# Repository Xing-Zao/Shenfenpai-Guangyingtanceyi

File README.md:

# 灵笼身份牌和光影探测仪软硬件开源资料

[灵笼身份牌](https://www.bilibili.com/video/BV1do4y1f7v5) 和 灵笼光[影探测仪](https://www.bilibili.com/video/BV1FK411F7UJ)的配套软硬件资料。

## 如何找到文件
- Light_detector 光影探测仪全部资料
- Badge 身份牌全部资料

每个文件夹下面都包含以下文件：
### 00_Priority README
该目录下存放了该控制板项目的全部**技术文档**，对该项目的程序源码、PCB设计都有详细说明，请首先阅读。
>文档目前尚未编写完成
>
### 01_Firmware
该目录下存放了 **软件/程序** 相关的全部源文件

### 02_Electronics
该目录下存放了 **电路/PCB** 相关的全部源文件

### 04_others
即不属于 软件/程序 也不属于 电路/PCB，但和本项目相关的其它文件

###  README.txt
每个文件夹下都有该文档，请**首先阅读**。这包含有其所处文件夹的阅读索引及一些重要说明。

## 支持

资料还在修改中，为了获得最佳的配置和故障排除帮助，请使用以下资源：
- 哔哩哔哩：[猩造](https://space.bilibili.com/16614468/)  
- 微信加群：

## 许可协议

FeixueMask 是遵循 [GPL license](/LICENSE) 协议发行的，因为我们相信开放式开发。 GPL附带了权利和义务。 无论您使用 FeixueMask 固件作为开源产品还是封闭源产品的驱动程序，都必须保持 FeixueMask 开放，并且必须根据要求向最终用户提供兼容的 FeixueMask 源代码。 遵守 FeixueMask 许可证的最直接方法是在 Github 上制作 FeixueMask 的分支，执行您的修改，并将用户引导到您修改后的分支。

虽然我们不能禁止在具有封闭源代码或有专利保护的产品中使用此代码，但我们还是希望您选择其他固件，或者最好自己制作。

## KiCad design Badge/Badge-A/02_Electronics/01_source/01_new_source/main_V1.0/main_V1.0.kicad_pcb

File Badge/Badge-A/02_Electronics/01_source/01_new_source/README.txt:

A1.0  2020-08-18
  原理图错误：
    1. Q1 引脚1、2颠倒（main、LED）
    2. RX接MCU引脚错误，应接PA10（main）
    3. 电容C2~5 值错误，应为 0.1uF（main）

V1.0  2020-08-21
   版本更新：
     1. 修复上一版设计错误（main、LED）
     2. LED灯板重新设计，三色灯改为单色灯（LED）
  版本错误：

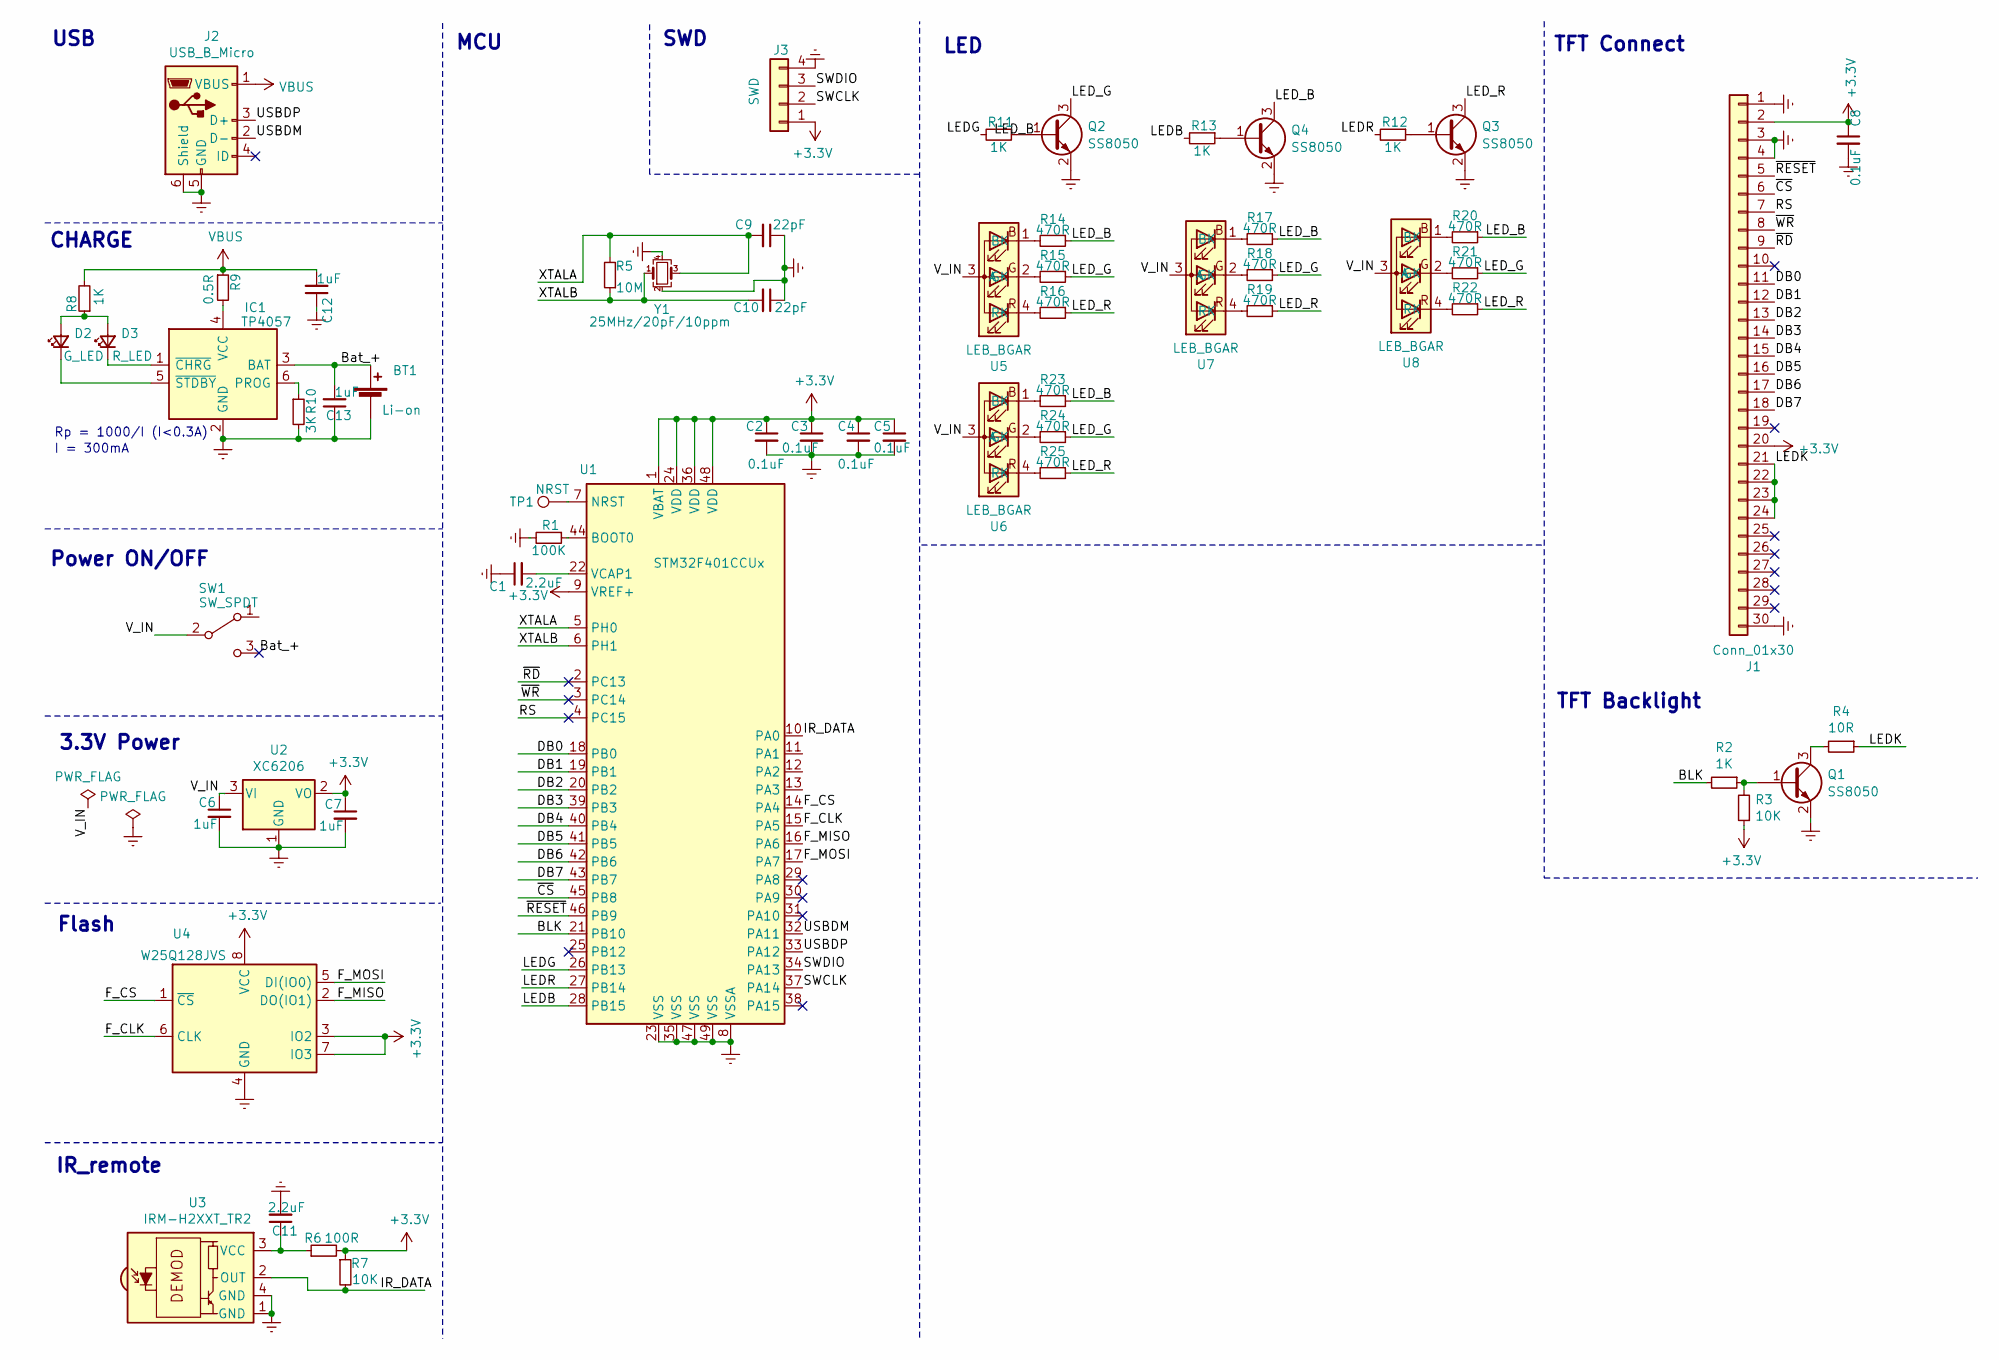
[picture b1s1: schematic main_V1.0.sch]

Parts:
BT1: Li-on; Pad-2.2mm_1.5x1.5
C1, C11: 2.2uF; C_0603_1608Metric
C2, C3, C4, C5, C8: 0.1uF; C_0402_1005Metric
C6, C7, C12, C13: 1uF; C_0603_1608Metric
C9, C10: 22pF; C_0603_1608Metric
D2: G_LED; LED_0603_1608Metric
D3: R_LED; LED_0603_1608Metric
IC1: TP4057; SOT-23-6; Manufacturer_Part_Number TP4057-42-SOT26-R
J1: Conn_01x30; FFC-1x30-1MP_P0.5mm_Horizontal
J2: USB_B_Micro; USB_Micro-B_Molex_Sink
J3: SWD; Con-1x4-P1.25mm
Q1, Q2, Q3, Q4: SS8050; SOT-23
R1: 100K; R_0603_1608Metric
R2, R8, R11, R12, R13: 1K; R_0402_1005Metric
R3, R7: 10K; R_0603_1608Metric
R4: 10R; R_0603_1608Metric
R5: 10M; R_0603_1608Metric
R6: 100R; R_0603_1608Metric
R9: 0.5R; R_0805_2012Metric
R10: 3K; R_0603_1608Metric
R14, R15, R16, R17, R18, R19, R20, R21, R22, R23, R24, R25: 470R; R_0402_1005Metric
SW1: SW_SPDT; MSKT-12C00-switch-smd
TP1: NRST; TestPoint_Pad_D1.0mm
U1: STM32F401CCUx; QFN-48-1EP_7x7mm_P0.5mm_EP5.6x5.6mm
U2: XC6206; SOT-23
U3: IRM-H2XXT_TR2
U4: W25Q128JVS; SON127P800X600X80-9N-D
U5, U6, U7, U8: LEB_BGAR; RGB-3510-Side-Common_anode
Y1: 25MHz/20pF/10ppm; Crystal_SMD_2520-4Pin_2.5x2.0mm

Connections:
+3V3: C2.1, C3.1, C4.1, C5.1, C7.1, C8.1, J1.2, J1.20, J3.1, R3.1, R6.2, R7.1, U1.1 (VBAT), U1.9 (VREF+), U1.24 (VDD), U1.36 (VDD), U1.48 (VDD), U2.2 (VO), U4.3 (IO2), U4.7 (IO3), U4.8 (VCC)
/BLK: R2.2, U1.21 (PB10)
/Bat_+: BT1.1 (+), C13.2, IC1.3 (BAT), SW1.3 (C)
/DB0: J1.11, U1.18 (PB0)
/DB1: J1.12, U1.19 (PB1)
/DB2: J1.13, U1.20 (PB2)
/DB3: J1.14, U1.39 (PB3)
/DB4: J1.15, U1.40 (PB4)
/DB5: J1.16, U1.41 (PB5)
/DB6: J1.17, U1.42 (PB6)
/DB7: J1.18, U1.43 (PB7)
/F_CLK: U1.15 (PA5), U4.6 (CLK)
/F_CS: U1.14 (PA4), U4.1 (~CS)
/F_MISO: U1.16 (PA6), U4.2 (DO(IO1))
/F_MOSI: U1.17 (PA7), U4.5 (DI(IO0))
/IR_DATA: R7.2, U1.10 (PA0), U3.2 (OUT)
/LEDB: R13.2, U1.28 (PB15)
/LEDG: R11.2, U1.26 (PB13)
/LEDK: J1.21, J1.22, J1.23, J1.24, R4.1
/LEDR: R12.2, U1.27 (PB14)
/LED_B: Q4.3 (C), R14.1, R17.1, R20.1, R23.1
/LED_G: Q2.3 (C), R15.1, R18.1, R21.1, R24.1
/LED_R: Q3.3 (C), R16.1, R19.1, R22.1, R25.1
/RS: J1.7, U1.4 (PC15)
/SWCLK: J3.2, U1.37 (PA14)
/SWDIO: J3.3, U1.34 (PA13)
/USBDM: J2.2 (D-), U1.32 (PA11)
/USBDP: J2.3 (D+), U1.33 (PA12)
/V_IN: C6.1, SW1.2 (B), U2.3 (VI), U5.3 (A), U6.3 (A), U7.3 (A), U8.3 (A)
/XTALA: C9.2, R5.2, U1.5 (PH0), Y1.3
/XTALB: C10.2, R5.1, U1.6 (PH1), Y1.1
/~CS: J1.6, U1.45 (PB8)
/~RD: J1.9, U1.2 (PC13)
/~RESET: J1.5, U1.46 (PB9)
/~WR: J1.8, U1.3 (PC14)
Earth: BT1.2 (-), C1.1, C2.2, C3.2, C4.2, C5.2, C6.2, C7.2, C8.2, C9.1, C10.1, C11.2, C12.1, C13.1, IC1.2 (GND), J1.1, J1.3, J1.4, J1.30, J2.5 (GND), J2.6 (Shield), J3.4, Q1.2 (E), Q2.2 (E), Q3.2 (E), Q4.2 (E), R1.2, R10.2, U1.8 (VSSA), U1.23 (VSS), U1.35 (VSS), U1.47 (VSS), U1.49 (VSS), U2.1 (GND), U3.1 (GND), U3.4 (GND), U4.4 (GND), Y1.2, Y1.4
unnamed: C1.2, U1.22 (VCAP1)
unnamed: C11.1, R6.1, U3.3 (VCC)
unnamed: D2.1 (K), IC1.5 (~STDBY)
unnamed: D2.2 (A), D3.2 (A), R8.1
unnamed: D3.1 (K), IC1.1 (~CHRG)
unnamed: IC1.4 (VCC), R9.2
unnamed: IC1.6 (PROG), R10.1
unnamed: Q1.1 (B), R2.1, R3.2
unnamed: Q1.3 (C), R4.2
unnamed: Q2.1 (B), R11.1
unnamed: Q3.1 (B), R12.1
unnamed: Q4.1 (B), R13.1
unnamed: R1.1, U1.44 (BOOT0)
unnamed: R14.2, U5.1 (BK)
unnamed: R15.2, U5.2 (GK)
unnamed: R16.2, U5.4 (RK)
unnamed: R17.2, U7.1 (BK)
unnamed: R18.2, U7.2 (GK)
unnamed: R19.2, U7.4 (RK)
unnamed: R20.2, U8.1 (BK)
unnamed: R21.2, U8.2 (GK)
unnamed: R22.2, U8.4 (RK)
unnamed: R23.2, U6.1 (BK)
unnamed: R24.2, U6.2 (GK)
unnamed: R25.2, U6.4 (RK)
unnamed: TP1.1, U1.7 (NRST)
VBUS: C12.2, J2.1 (VBUS), R8.2, R9.1

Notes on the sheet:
3.3V Power
Power ON/OFF
TFT Backlight
LED
TFT Connect
MCU
SWD
Rp = 1000/I (I<0.3A)
I = 300mA
USB
CHARGE
Flash
IR_remote

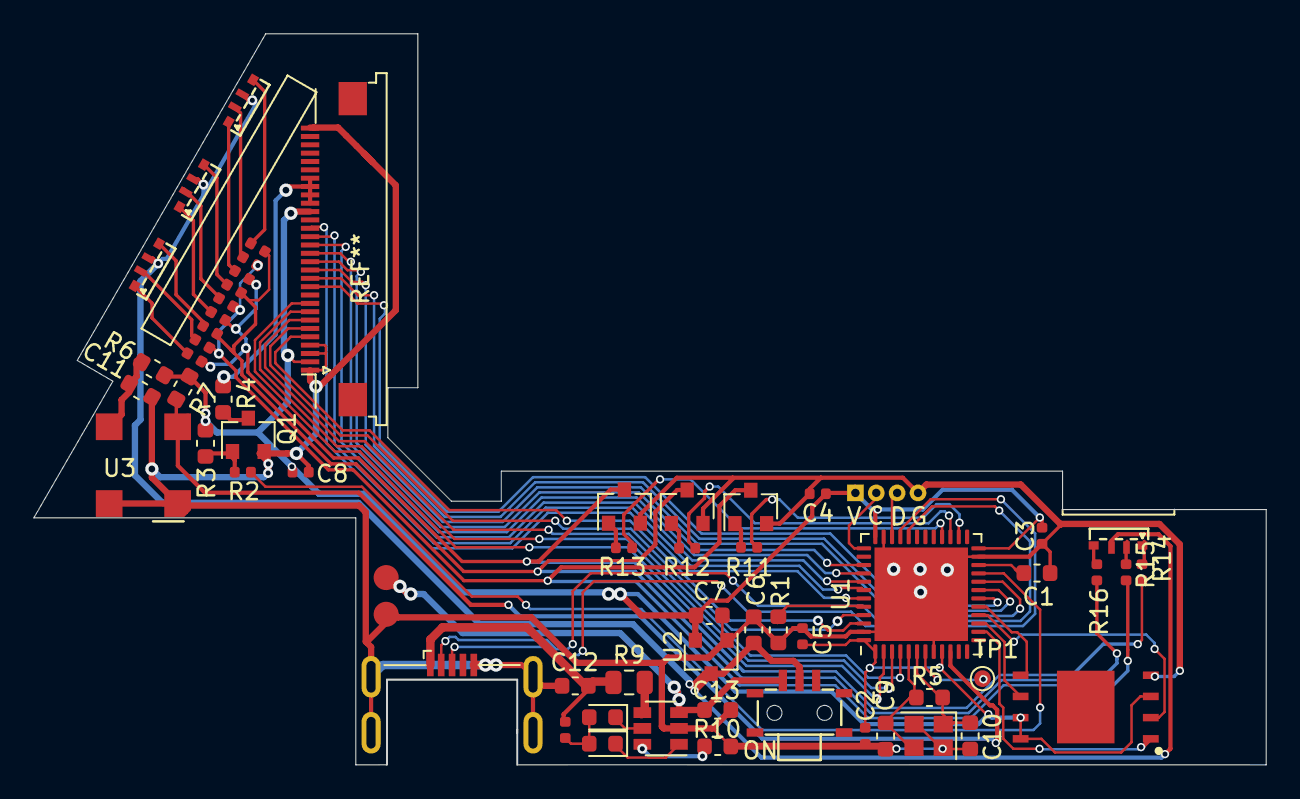
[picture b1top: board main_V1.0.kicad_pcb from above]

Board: 2 copper layers, 73.8 x 43.8 mm, 60 parts (0 on the bottom side), 63 nets.

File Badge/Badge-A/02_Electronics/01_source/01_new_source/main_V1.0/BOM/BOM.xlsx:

Reference | Quantity | Value | Footprint | Datasheet | Description | 采购建议
BT1 | 1 | Li-on | Pad-2.2mm_1.5x1.5 | ~ | 电池接口焊点，人工焊接 | 无需购买
C1 C11 | 2 | 2.2uF ±10% 6.3V/10V/16V | C_0603_1608Metric | ~ |  | 非指定厂家，符合：Value、Footprint 即可
C10 C9 | 2 | 22pF ±10% 6.3V/10V/16V | C_0603_1608Metric | ~ |  | 非指定厂家，符合：Value、Footprint 即可
C2 C3 C4 C5 C8 | 5 | 0.1uF ±10% 6.3V/10V/16V | C_0402_1005Metric | ~ |  | 非指定厂家，符合：Value、Footprint 即可
C6 C7 C12 C13 | 4 | 1uF ±10% 6.3V/10V/16V | C_0603_1608Metric | ~ |  | 非指定厂家，符合：Value、Footprint 即可
D2 | 1 | G_LED IF<25mA | LED_0603_1608Metric | ~ |  | 非指定厂家，符合：Value、Footprint 即可
D3 | 1 | R_LED IF<25mA | LED_0603_1608Metric | ~ |  | 非指定厂家，符合：Value、Footprint 即可
IC1 | 1 | TP4057 | SOT-23-6 | 见数据表：02-TP4057_2020-08-19.pdf | 锂电池充电芯片 | 指定厂家
J1 | 1 | Conn_01x30 | FFC-1x30-1MP_P0.5mm_Horizontal | 见数据表：03_FFCFPC连接器0.5MM间距30P卧贴抽拉式上接H1.2MM_2020-10-20.pdf | FFC 连接器 0.5mm间距 30P 卧贴抽拉式上接 H1.2mm | 指定厂家
J2 | 1 | USB_B_Micro | USB_Micro-B_Molex_Sink | 见数据表：04-MICRO_5SB型沉板式0.8四脚全插无导位有孔三边双卡端_2021-03-08.pdf | MICRO/5S B型沉板式0.8四脚全插无导位有孔三边双卡端 | 指定厂家
J3 | 1 | SWD | Con-1x4-P1.25mm | ~ | 下载调试接口，不焊接 | 无需购买
Q1 Q2 Q4 Q3 | 4 | SS8050 | SOT-23 | 见数据表：05-SS8050Y1200-350.pdf |  | 指定厂家
R1 | 1 | 100K ±5% 0.1W_1/16W | R_0603_1608Metric | ~ |  | 非指定厂家，符合：Value、Footprint 即可
R10 | 1 | 3K ±5% 0.1W_1/16W | R_0603_1608Metric | ~ |  | 非指定厂家，符合：Value、Footprint 即可
R14 R15 R16 R17 R18 R19 R20 R21 R22 R23 R24 R25 | 12 | 470R ±5% 0.1W_1/16W | R_0402_1005Metric | ~ |  | 非指定厂家，符合：Value、Footprint 即可
R2 R8 R11 R13 R12 | 5 | 1K ±5% 0.1W_1/16W | R_0402_1005Metric | ~ |  | 非指定厂家，符合：Value、Footprint 即可
R3 R7 | 2 | 10K ±5% 0.1W_1/16W | R_0603_1608Metric | ~ |  | 非指定厂家，符合：Value、Footprint 即可
R4 | 1 | 10R ±5% 0.1W_1/16W | R_0603_1608Metric | ~ |  | 非指定厂家，符合：Value、Footprint 即可
R5 | 1 | 10M ±5% 0.1W_1/16W | R_0603_1608Metric | ~ |  | 非指定厂家，符合：Value、Footprint 即可
R6 | 1 | 100R ±5% 0.1W_1/16W | R_0603_1608Metric | ~ |  | 非指定厂家，符合：Value、Footprint 即可
R9 | 1 | 0.5R ±5% 0.1W_1/16W | R_0805_2012Metric | ~ |  | 非指定厂家，符合：Value、Footprint 即可
SW1 | 1 | SW_SPDT | MSKT-12C00-switch-smd | 见数据表：10-开关规格.png | 侧贴拨动开关 | 指定厂家，淘宝：温州一键电子科技，型号MSKT-12C00 黑色
TP1 | 1 | NRST | TestPoint_Pad_D1.0mm | ~ | 测试焊点，不焊接 | 无需购买
U1 | 1 | STM32F401CCUx | QFN-48-1EP_7x7mm_P0.5mm_EP5.6x5.6mm | 见数据表：06-STM32F401CCU6_2016-08-16.pdf | 主控芯片，型号 STM32F401CCU6 | 指定厂家
U2 | 1 | XC6206 | SOT-23 | 见数据表：07-XC6206P302MR.pdf | 稳压降压芯片 | 指定厂家
U3 | 1 | IRM-H2XXT_TR2 | IRM-H2XXT_TR2 | 见数据表：08-红外线接收头38KHZ贴片_2017-09-18.PDF | 红外接收头 | 指定厂家
U4 | 1 | W25Q128JVS | SON127P800X600X80-9N-D | 见数据表：09-W25Q64JVZEIQ_2020-06-23.PDF | flash芯片，型号W25Q64JVIQ，封装WSON 8x6mm | 指定厂家
U5 U7 U8 U6 | 4 | LEB_BGAR | RGB-3510-Side-Common_anode | 见数据表：11-3510侧发RGB全彩_2020-09-04.PDF | 侧贴RGB全彩 | 指定厂家
Y1 | 1 | 25MHz/20pF/10ppm | Crystal_SMD_2520-4Pin_2.5x2.0mm | 见数据表：12-25M20PPM20PF-30+85℃_2018-07-26.PDF |  | 指定厂家
其它原件
 | 1 | 锂电池 | 尺寸：20x10x3mm 容量40mAh，带保护板 |  |  | 指定厂家，淘宝：裕辉达玩具数码电池户，型号301020 50mAh，带保护板
 | 1 | 1.9寸显示屏 | 1.9寸长条形IPS全视角170*320分辨率MCU接口 | 见数据表：13-TL019FQV01-B1263A_specification.pdf |  | 指定厂家，淘宝：深圳市显创液晶显示有限公司 型号：1.9寸长条形显示屏IPS全视角170*320分辨率
 | 1 | 背光板 | 18*8*1.3 |  | RGB侧面显示匀光板，需手工裁切 | 指定厂家，淘宝：深圳市宝晖光电 型号：18*8*1.3 白色背光板

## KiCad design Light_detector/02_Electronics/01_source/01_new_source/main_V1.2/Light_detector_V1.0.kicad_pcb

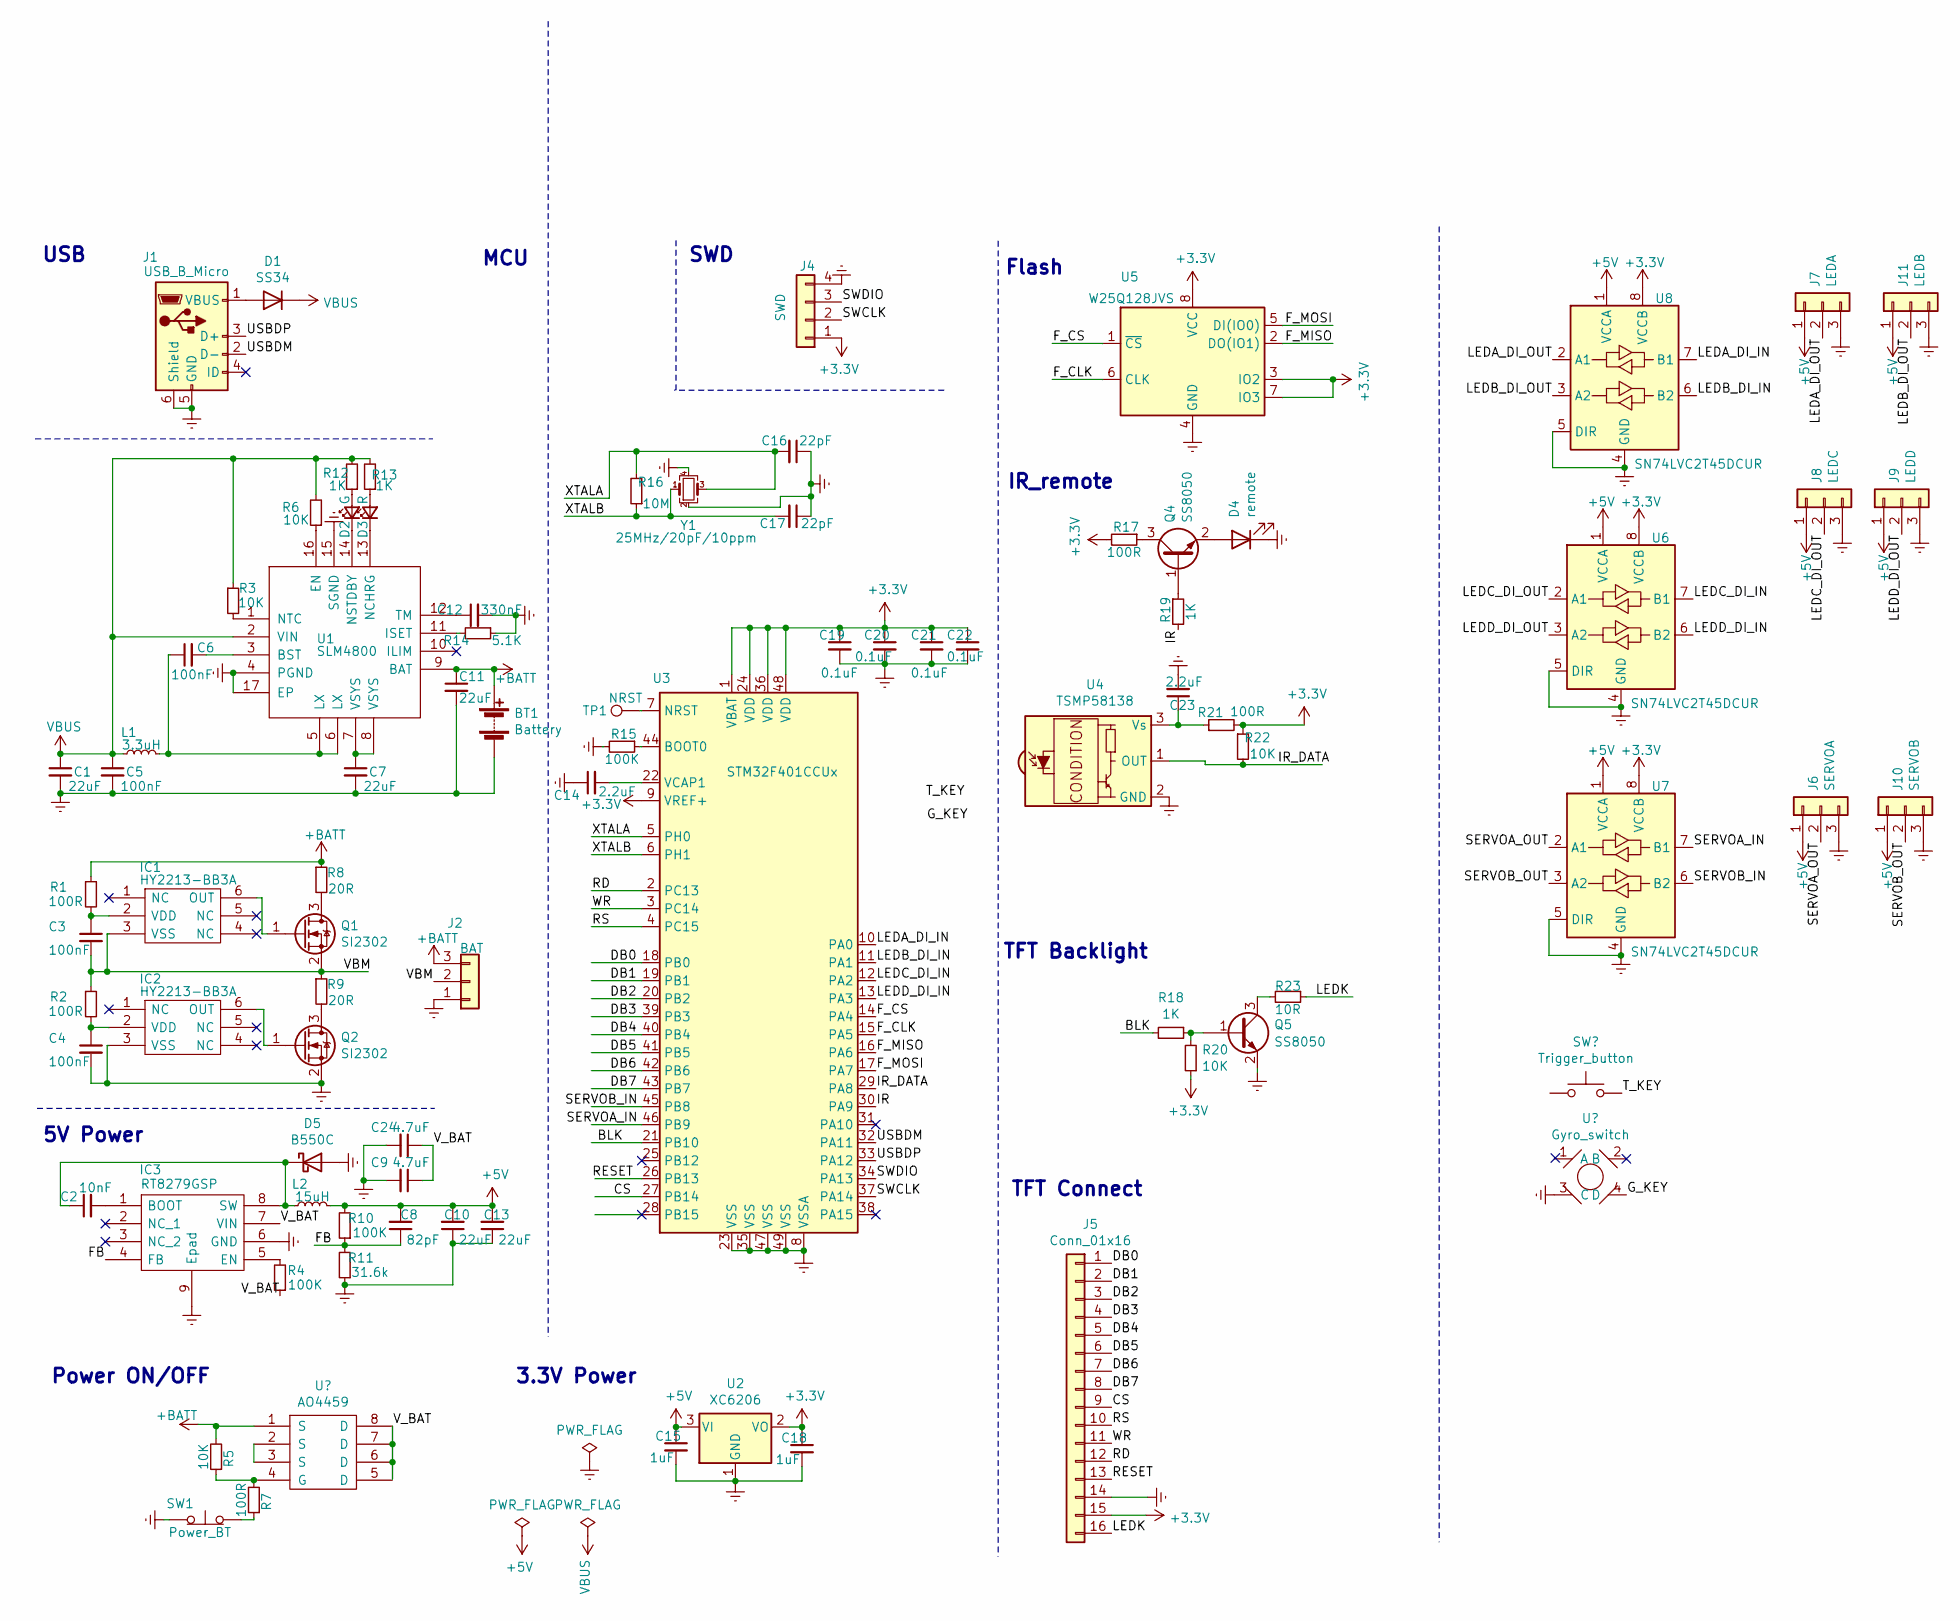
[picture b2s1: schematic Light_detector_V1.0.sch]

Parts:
BT1: Battery; JWT_A3963_1x02_P3.96mm_Vertical
C1, C7, C10, C11, C13: 22uF; C_1206_3216Metric
C2: 10nF; C_0402_1005Metric
C3, C4, C5, C6: 100nF; C_0402_1005Metric
C8: 82pF; C_0402_1005Metric
C9, C24: 4.7uF; C_1206_3216Metric
C12: 330nF; C_0402_1005Metric
C14, C23: 2.2uF; C_0603_1608Metric
C15, C18: 1uF; C_0603_1608Metric
C16, C17: 22pF; C_0402_1005Metric
C19, C20, C21, C22: 0.1uF; C_0402_1005Metric
D1: SS34; D_SMA
D2: G; LED_0603_1608Metric
D3: R; LED_0603_1608Metric
D4: remote; Con-2.5mm_0.9x1.7
D5: B550C; D_SMC
IC1, IC2: HY2213-BB3A; SOT95P280X140-6N; Manufacturer_Part_Number HY2213-BB3A
IC3: RT8279GSP; Diodes_SO-8EP; Manufacturer_Part_Number RT8279GSP
J1: USB_B_Micro; USB_Micro-B_Molex-105017-0001
J2: BAT; JST_XH_S3B-XH-A-1_1x03_P2.50mm_Horizontal
J4: SWD; PinHeader_1x04_P1.27mm_Vertical
J5: Conn_01x16; TE_1-1734839-6_1x16-1MP_P0.5mm_Horizontal
J6: SERVOA; PinHeader_1x03_P2.54mm_Horizontal
J7: LEDA; JST_XH_S3B-XH-A-1_1x03_P2.50mm_Horizontal
J8: LEDC; JST_XH_S3B-XH-A-1_1x03_P2.50mm_Horizontal
J9: LEDD; JST_XH_S3B-XH-A-1_1x03_P2.50mm_Horizontal
J10: SERVOB; PinHeader_1x03_P2.54mm_Horizontal
J11: LEDB; JST_XH_S3B-XH-A-1_1x03_P2.50mm_Horizontal
L1: 3.3uH; L_Sumida_CDMC6D28_7.25x6.5mm
L2: 15uH; L_Neosid_SM-PIC1004H
Q1, Q2: SI2302; SOT-23
Q4, Q5: SS8050; SOT-23
R1, R2, R7: 100R; R_0402_1005Metric
R3, R5, R6, R20, R22: 10K; R_0402_1005Metric
R4, R10, R15: 100K; R_0402_1005Metric
R8, R9: 20R; R_2512_6332Metric
R11: 31.6k; R_0402_1005Metric
R12, R13, R18, R19: 1K; R_0402_1005Metric
R14: 5.1K; R_0402_1005Metric
R16: 10M; R_0402_1005Metric
R17, R21: 100R; R_0603_1608Metric
R23: 10R; R_0603_1608Metric
SW1: Power_BT; JST_XH_S2B-XH-A-1_1x02_P2.50mm_Horizontal
TP1: NRST; TestPoint_Pad_D1.0mm
U1: SLM4800; QFN-16-1EP_4x4mm_P0.65mm_EP2.1x2.1mm_ThermalVias
U2: XC6206; SOT-23
U3: STM32F401CCUx; QFN-48-1EP_7x7mm_P0.5mm_EP5.6x5.6mm
U4: TSMP58138; Vishay_MINICAST-3Pin
U5: W25Q128JVS; SON127P800X600X80-9N-D
U6, U7, U8: SN74LVC2T45DCUR; VSSOP-8_2.4x2.1mm_P0.5mm
Y1: 25MHz/20pF/10ppm; Crystal_SMD_2520-4Pin_2.5x2.0mm

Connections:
+3V3: C18.1, C19.1, C20.1, C21.1, C22.1, J4.1, J5.15, R17.2, R20.1, R21.2, R22.1, U2.2 (VO), U3.1 (VBAT), U3.9 (VREF+), U3.24 (VDD), U3.36 (VDD), U3.48 (VDD), U5.3 (IO2), U5.7 (IO3), U5.8 (VCC), U6.8 (VCCB), U7.8 (VCCB), U8.8 (VCCB)
+5V: C8.2, C10.2, C13.2, C15.1, J6.1, J7.1, J8.1, J9.1, J10.1, J11.1, L2.2, R10.2, U2.3 (VI), U6.1 (VCCA), U7.1 (VCCA), U8.1 (VCCA)
+BATT: BT1.1 (+), C11.1, J2.3, R1.1, R5.2, R8.1, U1.9 (BAT); also elsewhere on the board
/BLK: R18.2, U3.21 (PB10)
/CS: J5.9, U3.27 (PB14)
/DB0: J5.1, U3.18 (PB0)
/DB1: J5.2, U3.19 (PB1)
/DB2: J5.3, U3.20 (PB2)
/DB3: J5.4, U3.39 (PB3)
/DB4: J5.5, U3.40 (PB4)
/DB5: J5.6, U3.41 (PB5)
/DB6: J5.7, U3.42 (PB6)
/DB7: J5.8, U3.43 (PB7)
/FB: C8.1, IC3.4 (FB), R10.1, R11.2
/F_CLK: U3.15 (PA5), U5.6 (CLK)
/F_CS: U3.14 (PA4), U5.1 (~CS)
/F_MISO: U3.16 (PA6), U5.2 (DO(IO1))
/F_MOSI: U3.17 (PA7), U5.5 (DI(IO0))
/IR: R19.2, U3.30 (PA9)
/IR_DATA: R22.2, U3.29 (PA8), U4.1 (OUT)
/LEDA_DI_IN: U3.10 (PA0), U8.7 (B1)
/LEDA_DI_OUT: J7.2, U8.2 (A1)
/LEDB_DI_IN: U3.11 (PA1), U8.6 (B2)
/LEDB_DI_OUT: J11.2, U8.3 (A2)
/LEDC_DI_IN: U3.12 (PA2), U6.7 (B1)
/LEDC_DI_OUT: J8.2, U6.2 (A1)
/LEDD_DI_IN: U3.13 (PA3), U6.6 (B2)
/LEDD_DI_OUT: J9.2, U6.3 (A2)
/LEDK: J5.16, R23.1
/RD: J5.12, U3.2 (PC13)
/RESET: J5.13, U3.26 (PB13)
/RS: J5.10, U3.4 (PC15)
/SERVOA_IN: U3.46 (PB9), U7.7 (B1)
/SERVOA_OUT: J6.2, U7.2 (A1)
/SERVOB_IN: U3.45 (PB8), U7.6 (B2)
/SERVOB_OUT: J10.2, U7.3 (A2)
/SWCLK: J4.2, U3.37 (PA14)
/SWDIO: J4.3, U3.34 (PA13)
/USBDM: J1.2 (D-), U3.32 (PA11)
/USBDP: J1.3 (D+), U3.33 (PA12)
/VBM: C3.2, IC1.3 (VSS), J2.2, Q1.2 (S), R2.1, R9.1
/V_BAT: C9.1, C24.1, IC3.7 (VIN), R4.1; also elsewhere on the board
/WR: J5.11, U3.3 (PC14)
/XTALA: C16.2, R16.2, U3.5 (PH0), Y1.3
/XTALB: C17.2, R16.1, U3.6 (PH1), Y1.1
Earth: BT1.2 (-), C1.2, C4.2, C5.2, C7.2, C9.2, C10.1, C11.2, C12.2, C13.1, C14.1, C15.2, C16.1, C17.1, C18.2, C19.2, C20.2, C21.2, C22.2, C23.2, C24.2, D4.1 (K), D5.2 (A), IC2.3 (VSS), IC3.6 (GND), IC3.9 (Epad), J1.5 (GND), J1.6 (Shield), J2.1, J4.4, J5.14, J6.3, J7.3, J8.3, J9.3, J10.3, J11.3, Q2.2 (S), Q5.2 (E), R11.1, R14.1, R15.2, SW1.1 (A), U1.4 (PGND), U1.15 (SGND), U1.17 (EP), U2.1 (GND), U3.8 (VSSA), U3.23 (VSS), U3.35 (VSS), U3.47 (VSS), U3.49 (VSS), U4.2 (GND), U5.4 (GND), U6.4 (GND), U6.5 (DIR), U7.4 (GND), U7.5 (DIR), U8.4 (GND), U8.5 (DIR), Y1.2, Y1.4
unnamed: C2.1, D5.1 (K), IC3.8 (SW), L2.1
unnamed: C2.2, IC3.1 (BOOT)
unnamed: C3.1, IC1.2 (VDD), R1.2
unnamed: C4.1, IC2.2 (VDD), R2.2
unnamed: C6.1, L1.2, U1.5 (LX), U1.6 (LX)
unnamed: C6.2, U1.3 (BST)
unnamed: C7.1, U1.7 (VSYS), U1.8 (VSYS)
unnamed: C12.1, U1.12 (TM)
unnamed: C14.2, U3.22 (VCAP1)
unnamed: C23.1, R21.1, U4.3 (Vs)
unnamed: D1.2 (A), J1.1 (VBUS)
unnamed: D2.1 (K), U1.14 (NSTDBY)
unnamed: D2.2 (A), R12.1
unnamed: D3.1 (K), U1.13 (NCHRG)
unnamed: D3.2 (A), R13.1
unnamed: D4.2 (A), Q4.2 (E)
unnamed: IC1.6 (OUT), Q1.1 (G)
unnamed: IC2.6 (OUT), Q2.1 (G)
unnamed: IC3.5 (EN), R4.2
unnamed: Q1.3 (D), R8.2
unnamed: Q2.3 (D), R9.2
unnamed: Q4.1 (B), R19.1
unnamed: Q4.3 (C), R17.1
unnamed: Q5.1 (B), R18.1, R20.2
unnamed: Q5.3 (C), R23.2
unnamed: R3.2, U1.1 (NTC)
unnamed 81: R5.1, R7.2; also elsewhere on the board
unnamed: R6.1, U1.16 (EN)
unnamed: R7.1, SW1.2 (B)
unnamed: R14.2, U1.11 (ISET)
unnamed: R15.1, U3.44 (BOOT0)
unnamed: TP1.1, U3.7 (NRST)
VBUS: C1.1, C5.1, D1.1 (K), L1.1, R3.1, R6.2, R12.2, R13.2, U1.2 (VIN)

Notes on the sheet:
3.3V Power
Power ON/OFF
TFT Connect
MCU
SWD
USB
Flash
5V Power
TFT Backlight
IR_remote

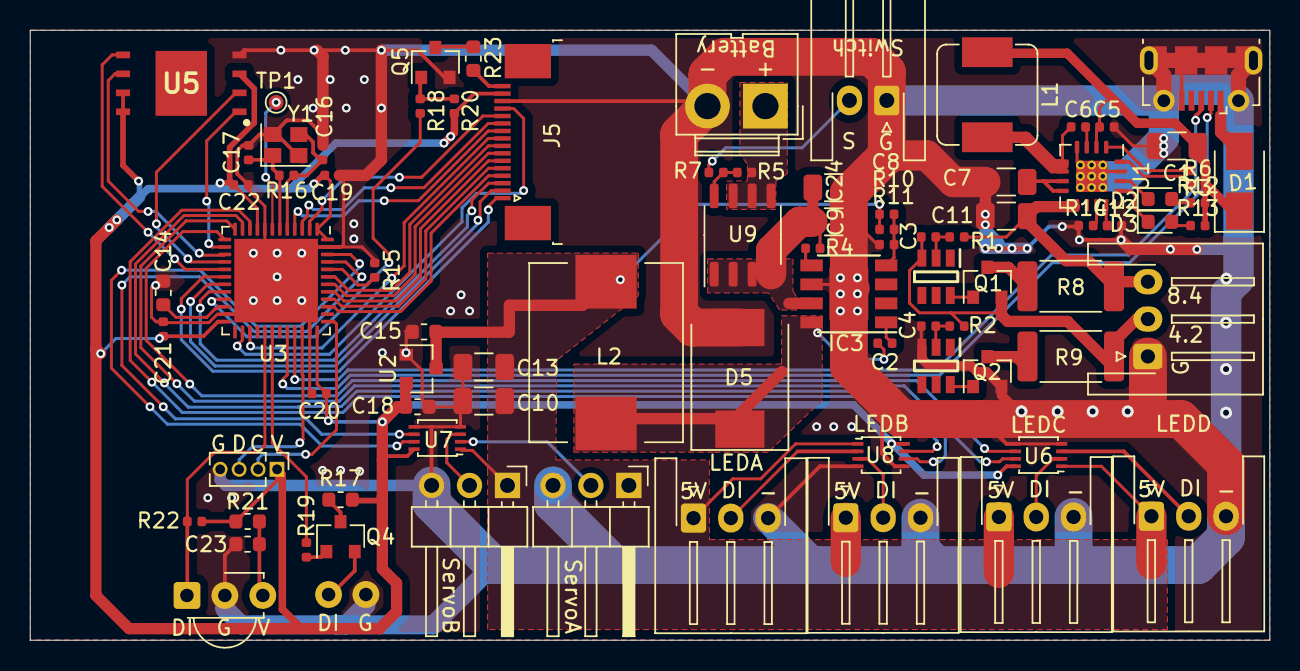
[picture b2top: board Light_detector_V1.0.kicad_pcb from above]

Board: 2 copper layers, 83.0 x 40.9 mm, 84 parts (0 on the bottom side), 79 nets.

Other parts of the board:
U9: AO4459; SOP-8_3.9x4.9mm_P1.27mm

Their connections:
+BATT: U9.5, U9.6, U9.7; also elsewhere on the board
/V_BAT: U9.1, U9.2, U9.3, U9.4; also elsewhere on the board
unnamed 81: U9.8; also elsewhere on the board

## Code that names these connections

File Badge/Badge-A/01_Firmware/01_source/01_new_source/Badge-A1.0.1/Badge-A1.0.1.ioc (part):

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PC13-ANTI_TAMP.GPIO_Speed=GPIO_SPEED_FREQ_LOW
PB10.PinState=GPIO_PIN_SET
PA6.Mode=Full_Duplex_Master
Mcu.UserName=STM32F401CCUx
PB10.GPIO_Speed=GPIO_SPEED_FREQ_VERY_HIGH
PB10.GPIO_PuPd=GPIO_PULLUP
PB2.GPIO_Speed=GPIO_SPEED_FREQ_VERY_HIGH
PA11.Mode=Device_Only
PB13.Signal=GPIO_Output
PB15.Signal=GPIO_Output
PB3.GPIO_Speed=GPIO_SPEED_FREQ_VERY_HIGH
RCC.SYSCLKSource=RCC_SYSCLKSOURCE_PLLCLK
PB5.GPIOParameters=GPIO_Speed,GPIO_PuPd
PB4.GPIOParameters=GPIO_Speed,GPIO_PuPd
PA12.Signal=USB_OTG_FS_DP
PH0\ -\ OSC_IN.Signal=RCC_OSC_IN
PB1.GPIO_PuPd=GPIO_PULLUP
PB6.Signal=GPIO_Output
PA0-WKUP.GPIOParameters=GPIO_Speed,GPIO_PuPd
RCC.HSE_VALUE=25000000
PA0-WKUP.GPIO_Speed=GPIO_SPEED_FREQ_VERY_HIGH
PA4.GPIO_PuPd=GPIO_PULLUP
PB2.Signal=GPIO_Output
PC13-ANTI_TAMP.Signal=GPIO_Output
PA4.GPIO_Speed=GPIO_SPEED_FREQ_VERY_HIGH
PB0.GPIOParameters=GPIO_Speed,GPIO_PuPd
PB3.GPIO_PuPd=GPIO_PULLUP
PB1.GPIO_Speed=GPIO_SPEED_FREQ_VERY_HIGH
PA14.Mode=Serial_Wire
PB3.GPIOParameters=GPIO_Speed,GPIO_PuPd
PB7.Signal=GPIO_Output
PB6.GPIOParameters=GPIO_Speed,GPIO_PuPd
PB2.GPIO_PuPd=GPIO_PULLUP
PC14-OSC32_IN.GPIOParameters=GPIO_PuPd
Mcu.Package=UFQFPN48
PB9.Signal=GPIO_Output
PB1.Signal=GPIO_Output
PA6.Signal=SPI1_MISO
PB9.GPIO_PuPd=GPIO_PULLUP
PB5.GPIO_Speed=GPIO_SPEED_FREQ_VERY_HIGH
PB9.GPIO_Speed=GPIO_SPEED_FREQ_VERY_HIGH
PB10.GPIOParameters=GPIO_Speed,PinState,GPIO_PuPd
PC15-OSC32_OUT.GPIOParameters=GPIO_PuPd
PA4.GPIO_Label=SPI1_CS
PB4.Signal=GPIO_Output
PC13-ANTI_TAMP.GPIOParameters=GPIO_Speed,GPIO_PuPd
PA5.Mode=Full_Duplex_Master
PB7.GPIO_Speed=GPIO_SPEED_FREQ_VERY_HIGH
PB7.GPIO_PuPd=GPIO_PULLUP
PB8.GPIOParameters=GPIO_Speed,GPIO_PuPd
PA7.Mode=Full_Duplex_Master
PC13-ANTI_TAMP.GPIO_PuPd=GPIO_PULLUP
PB6.GPIO_PuPd=GPIO_PULLUP
PH1\ -\ OSC_OUT.Mode=HSE-External-Oscillator
PB8.GPIO_PuPd=GPIO_PULLUP
PC14-OSC32_IN.Signal=GPIO_Output
PA0-WKUP.Signal=S_TIM2_CH1_ETR
PB9.GPIOParameters=GPIO_Speed,GPIO_PuPd
PB0.GPIO_Speed=GPIO_SPEED_FREQ_VERY_HIGH
PA13.Signal=SYS_JTMS-SWDIO
PH0\ -\ OSC_IN.Mode=HSE-External-Oscillator
PB7.GPIOParameters=GPIO_Speed,GPIO_PuPd
PB2.GPIOParameters=GPIO_Speed,GPIO_PuPd
PB4.GPIO_PuPd=GPIO_PULLUP
PC15-OSC32_OUT.Signal=GPIO_Output
PB10.Signal=GPIO_Output
PB14.Signal=GPIO_Output
PA5.Signal=SPI1_SCK
PH1\ -\ OSC_OUT.Signal=RCC_OSC_OUT
board=custom
PB4.GPIO_Speed=GPIO_SPEED_FREQ_VERY_HIGH
PC15-OSC32_OUT.GPIO_PuPd=GPIO_PULLUP
PA4.GPIOParameters=GPIO_Speed,GPIO_PuPd,GPIO_Label
PA13.Mode=Serial_Wire
Mcu.Name=STM32F401C(B-C)Ux
PB3.Signal=GPIO_Output
PA4.Signal=GPIO_Output
RCC.SYSCLKFreq_VALUE=60000000
PB5.Signal=GPIO_Output
PA12.Mode=Device_Only
PB5.GPIO_PuPd=GPIO_PULLUP
PA11.Signal=USB_OTG_FS_DM
PA14.Signal=SYS_JTCK-SWCLK
PB8.Signal=GPIO_Output
PA0-WKUP.GPIO_PuPd=GPIO_PULLUP
PC14-OSC32_IN.GPIO_PuPd=GPIO_PULLUP
PB6.GPIO_Speed=GPIO_SPEED_FREQ_VERY_HIGH
PB8.GPIO_Speed=GPIO_SPEED_FREQ_VERY_HIGH
PB0.Signal=GPIO_Output
PB0.GPIO_PuPd=GPIO_PULLUP
PB1.GPIOParameters=GPIO_Speed,GPIO_PuPd
PA7.Signal=SPI1_MOSI

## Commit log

2021-05-12 updata
2021-05-12 upload
2021-05-12 opload
